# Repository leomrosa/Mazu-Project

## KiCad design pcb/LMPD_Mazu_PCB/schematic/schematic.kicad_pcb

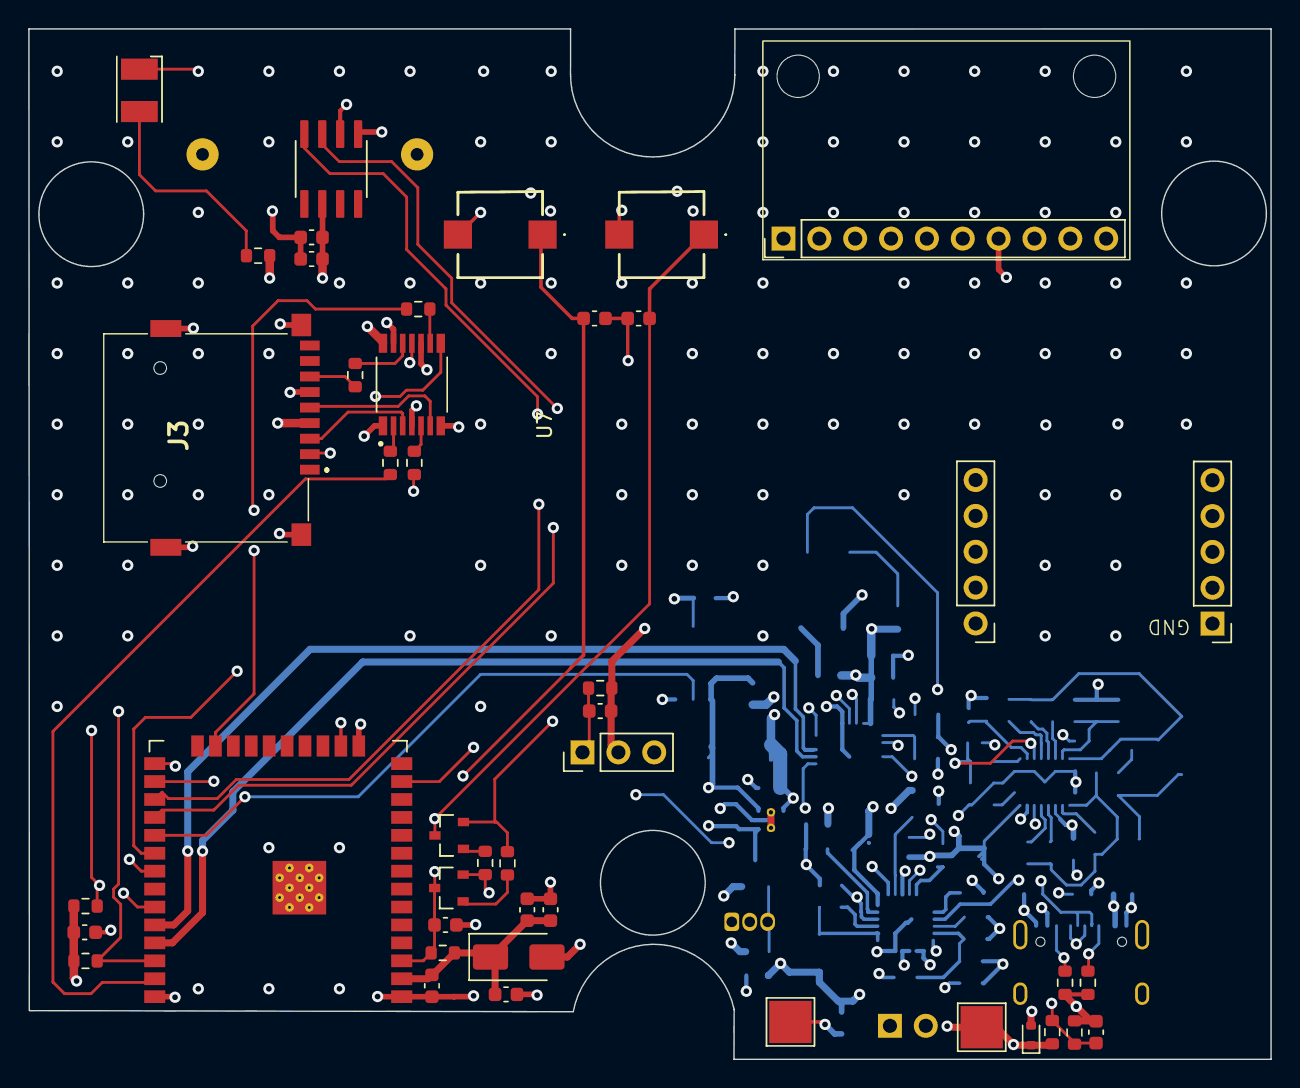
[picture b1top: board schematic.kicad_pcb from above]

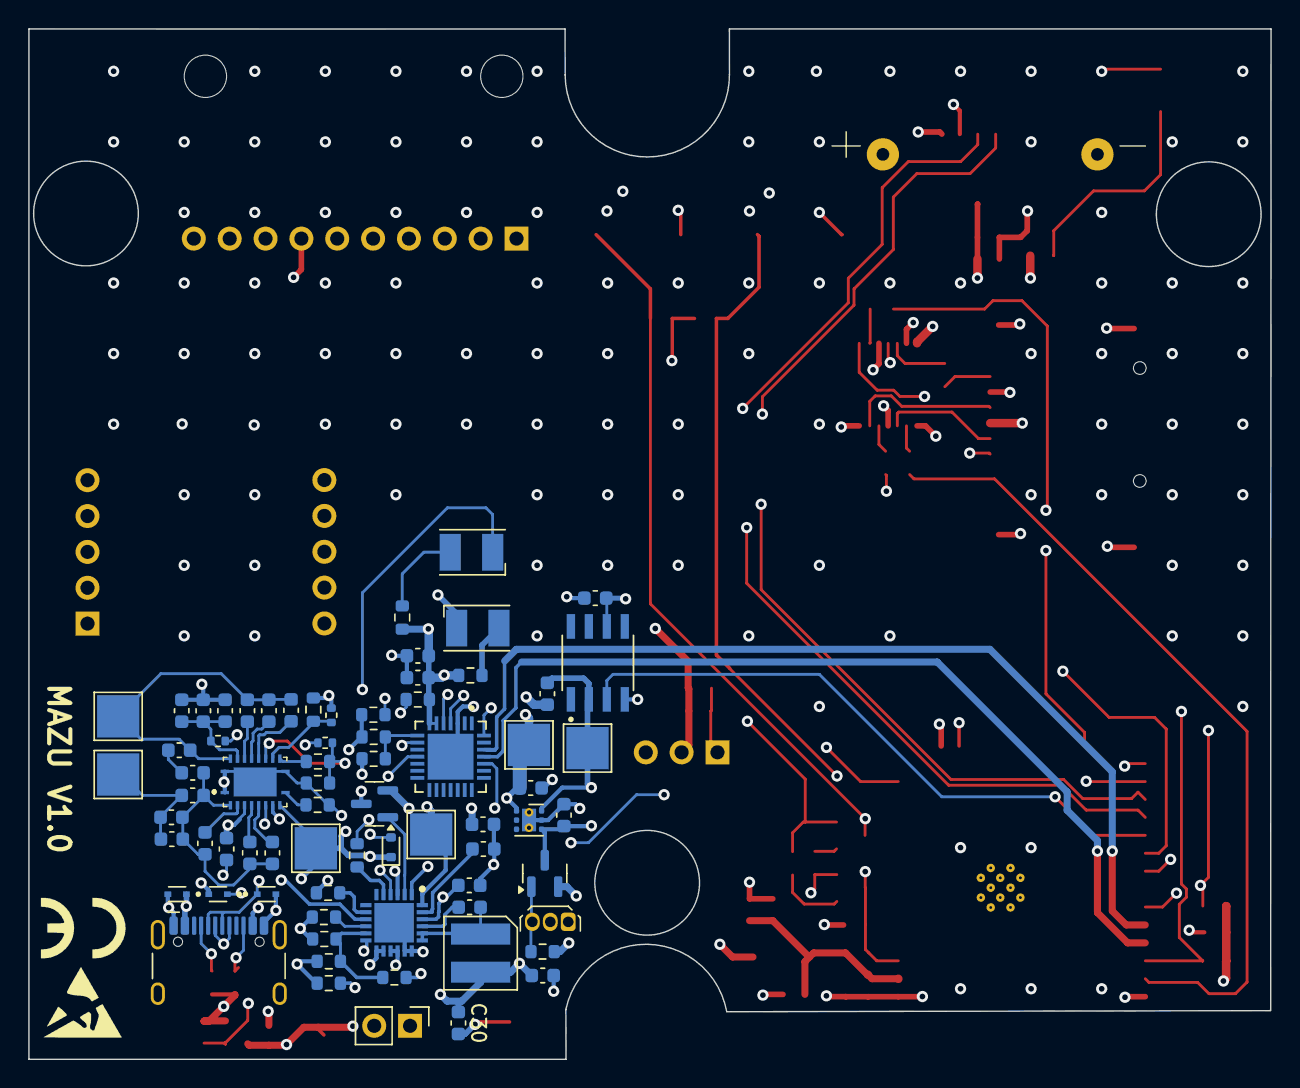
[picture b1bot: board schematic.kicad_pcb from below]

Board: 6 copper layers, 88.0 x 73.0 mm, 115 parts (72 on the bottom side), 77 nets.

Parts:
BT1: Battery_Cell; Panasonic BR1632
C1: 2.2u; C_0603_1608Metric
C2: 4.7u; C_0603_1608Metric
C3, C4, C5, C6, C7, C8, C11, C12, C16, C25, C31, C32, C33, C34, C36, C38: 100n; C_0603_1608Metric
C9, C30: 47u; C_0603_1608Metric
C10, C39: 470n; C_0603_1608Metric
C13: 1u; C_0603_1608Metric
C14, C15, C17, C19: 22n; C_0603_1608Metric
C18: 2.2n; C_0603_1608Metric
C20, C21, C22: 10n; C_0603_1608Metric
C23, C24, C26, C27, C35, C37: 10u; C_0603_1608Metric
C28: 47n; C_0603_1608Metric
C29: 4.7u - 10v; C_0603_1608Metric
D1, D5: CPDU12V0U-HF; D_SOD-523
D2, D3, D4: LESD5D5.0CT1G; TVS_LESD5D5.0CT1G
D6: VLMT3100-GS08; LED_PLCC-2_3.4x3.0mm_KA
D7, D8: VLMC3100-GS08; LED_PLCC-2_3.4x3.0mm_KA
D9: B340A-E3/61T; D_SMA
IC2: BQ25616RTWR; QFN50P400X400X80-25N-D
J1: Batt; PinHeader_1x02_P2.54mm_Vertical
J1_TMP1: Conn_01x03_Male; PinHeader_1x03_P2.54mm_Vertical
J2: GT-USB-7010ASV; USB_C_Receptacle_HCTL_HC-TYPE-C-16P-01A
J3: TF-15X15; TF15X15
L1: 1uH; inductor_bourns_4x4
Q1, Q2: SS8050-G; TRANS_SS8050-G
Q3: IRLML6344TRPBF; SOT-23
Q4: SSM3J338R,LF; SOT-23
R1, R2, R32: 5.1k; R_0603_1608Metric
R3, R4, R6, R8, R10, R11, R21, R28, R30, R34, R35, R39: 10k; R_0603_1608Metric
R5, R12, R13: 4.7k; R_0603_1608Metric
R7, R9, R31: 680; R_0603_1608Metric
R17, R18, R19, R20: 330; R_0603_1608Metric
R22, R23: 220; R_0603_1608Metric
R24: 2.4k; R_0603_1608Metric
R25, R26, R27: 12k; R_0402_1005Metric
R29: 560; R_0603_1608Metric
R33: 33k; R_0603_1608Metric
R36: 22.1k; R_0603_1608Metric
R37: 47.5k; R_0603_1608Metric
R38: 2k; R_0603_1608Metric
SW1, SW2: SW_Push; EVPASAC1A
TP1, TP2, TP3, TP4, TP5, TP6, TP7, TP8: TestPoint_Pad_3.0x3.0mm
U1: REF196GSZ-REEL; SOIC127P600X175-8N
U2: SS460S; TO-92Flat
U3: LP5912-3.3DRV; LP5912
U4: GY-9250
U5: 74LVC125APW,118; IC_74LVC125APW,118
U6: BQ51050BRHLR
U7: ESP32-WROOM-32D
U8: CP2102N-A02-GQFN28; QFN50P500X500X80-29N
U9: GPS-AIR530; GPS_Air530
U10: DS3231MZ+TRL; DS3231MZ_TRL

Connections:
/BATT: C13.1, D1.1 (A1), IC2.13 (BAT_1), IC2.14 (BAT_2), J1.2, R10.2, TP1.1, U6.4 (BAT)
/CTRL_GPIO: U1.3 (SHDN), U7.29 (IO5)
/DTR: Q2.2, R3.2, U8.28 (DTR)
/EN: C32.1, C33.1, Q1.3, R35.2, SW1.A1 (COM), U7.3 (EN)
/ESP32_WROOM_32D/IO14: C4.1, R10.1, R11.2, U7.13 (IO14)
/ESP32_WROOM_32D/VDD_3V3: C8.1, C9.1, C34.1, C35.1, D9.1 (K), R35.1, U7.2 (VDD)
/GPS_RXD: U7.28 (IO17), U9.7 (GPS_RXD)
/GPS_TXD: U7.27 (IO16), U9.6 (GPS_TXD)
/IIC_SCL: R12.2, U4.3 (SCL), U7.36 (IO22), U10.8 (SCL)
/IIC_SDA: R13.2, U4.4 (SDA), U7.33 (IO21), U10.7 (SDA)
/IO0: C36.1, Q2.3, SW2.A1 (COM), U7.25 (IO0)
/PRE_VCC: C30.1, C31.1, IC2.15 (SYS_1), IC2.16 (SYS_2), L1.2, Q4.2 (S), R8.2, U2.1 (IN)
/RTS: Q1.2, R4.2, U8.24 (RTS)
/SPI_CS: R19.1, U7.23 (IO15)
/SPI_MISO: U5.11 (4Y), U7.31 (IO19)
/SPI_MOSI: R17.1, U7.37 (IO23)
/SPI_SCK: R18.1, U7.30 (IO18)
/STAT: D7.1 (K), R28.1, U7.16 (IO13)
/TMP_DATA: C3.1, J1_TMP1.1, R5.1, U7.26 (IO4)
/UART_PROG_RX: U7.35 (TXD0/IO1), U8.25 (RXD)
/UART_PROG_TX: U7.34 (RXD0/IO3), U8.26 (TXD)
/USB5V: D4.1, D5.1 (A1), IC2.1 (VAC), J2.A4 (VBUS), J2.A9 (VBUS), J2.B4 (VBUS), J2.B9 (VBUS), Q3.3 (D), R36.1, TP3.1, U6.9 (AD)
/USBD+: D2.1, IC2.3 (D+), J2.A6 (D+), J2.B6 (D+), U8.4 (D+)
/USBD-: D3.1, IC2.4 (D-), J2.A7 (D-), J2.B7 (D-), U8.5 (D-)
/VCC_RAW: C1.1, C5.1, Q4.3 (D), TP7.1, U1.2 (VIN), U3.4 (EN), U3.6 (IN)
/VREF_3V3: C6.1, C7.1, C11.1, C12.1, C37.1, C38.1, D9.2 (A), J3.4 (VDD), R7.2, R9.2, R12.1, R13.1, R21.1, R38.1, TP8.1, U3.1 (OUT), U4.1 (VCC), U4.7 (ADO), U5.14 (VCC), U8.6 (VDD), U8.7 (VREGIN), U9.3 (3V3), U9.5 (VBACKUP), U10.2 (VCC)
/VREF_TMP_3V3: C2.1, C3.2, J1_TMP1.2, R5.2, U1.6 (VOUT)
/WRL_EN: IC2.9 (~CE), U6.8 (~AD-EN)
/batery_module/ACDRV: IC2.2 (ACDRV), Q3.1 (G)
/batery_module/VIN: C26.1, IC2.24 (VBUS), Q3.2 (S), TP4.1
/rtc_ds3231/BAT_CELL+: BT1.1 (+), U10.6 (VBAT)
/sd_card/CS_LLS: J3.2 (CD/DAT3), U5.8 (3Y)
/sd_card/DI_LLS: J3.3 (CMD), U5.3 (1Y)
/sd_card/DO_LLS: J3.7 (DAT0), R20.1
/sd_card/SCK_LLS: J3.5 (CLX), U5.6 (2Y)
/wireless_charging/AC1: C10.2, C14.1, C15.1, C16.2, C17.2, C18.2, C21.2, U6.2 (AC1)
/wireless_charging/CLAMP1: C10.1, U6.5 (CLAMP1)
/wireless_charging/CLAMP2: C39.1, U6.16 (CLAMP2)
/wireless_charging/COIL+: C14.2, C15.2, C16.1, TP6.1
/wireless_charging/COIL-: C19.2, C20.1, C22.2, C39.2, TP5.1, U6.19 (AC2)
/wireless_charging/NTC: R6.1, R25.1, U6.13 (TS/CTRL)
/wireless_charging/RECT: C23.1, C24.1, C25.1, R26.1, U6.18 (RECT)
/wireless_charging/TERM: R24.2, U6.10 (TERM)
/wireless_charging/~CHG_PIN: D6.1 (K), U6.7 (~CHG)
GNDREF: BT1.2 (-), C1.2, C2.2, C4.2, C5.2, C6.2, C7.2, C8.2, C9.2, C11.2, C12.2, C13.2, C23.2, C24.2, C25.2, C26.2, C27.2, C29.2, C30.2, C31.2, C32.2, C33.2, C34.2, C35.2, C36.2, C37.2, C38.2, D1.2 (A2), D2.2, D3.2, D4.2, D5.2 (A2), D8.1 (K), IC2.17 (GND_1), IC2.18 (GND_2), IC2.25 (EP), J1.1, J1_TMP1.3, J2.A1 (GND), J2.A12 (GND), J2.B1 (GND), J2.B12 (GND), J2.S1 (SHIELD), J3.6 (VSS), J3.MP1, J3.MP2, J3.MP3, J3.MP4, R1.1, R2.1, R6.2, R11.1, R23.1, R24.1, R25.2, R29.2, R30.2, R31.2, R33.1, R34.1, R37.2, R39.2, SW1.B1 (NO), SW2.B1 (NO), TP2.1, U1.4 (GND), U2.2, U3.5 (GND), U3.7 (EP), U4.2 (GND), U5.1 (1~OE), U5.4 (2~OE), U5.7 (GND), U5.10 (3~OE), U5.13 (4~OE), U6.1 (PGND), U6.11 (EN2), U6.20 (PGND), U6.21 (PGND), U7.1 (GND), U7.15 (GND), U7.38 (GND), U7.39 (GND), U8.3 (GND), U8.29 (GND), U9.1 (GND), U10.5 (GND)
unnamed: C18.1, C20.2
unnamed: D6.2 (A), R7.1
unnamed: D7.2 (A), R9.1
unnamed: D8.2 (A), R21.2
unnamed: C28.1, IC2.21 (BTST)
unnamed: IC2.10 (ICHG), R31.1
unnamed: IC2.8 (ILIM), R29.1
unnamed: C27.1, IC2.23 (PMID)
unnamed: C29.1, IC2.22 (REGN), R32.1
unnamed: IC2.5 (STAT), R28.2
unnamed: C28.2, IC2.19 (SW_1), IC2.20 (SW_2), L1.1
unnamed: IC2.11 (TS), R32.2, R33.2, R34.2
unnamed: IC2.12 (VSET), R30.1
unnamed: J2.A5 (CC1), R1.2
unnamed: J2.B5 (CC2), R2.2
unnamed: Q1.1, R3.1
unnamed: Q2.1, R4.1
unnamed: Q4.1 (G), R8.1, U2.3 (OUT)
unnamed: R26.2, R27.1
unnamed: R17.2, U5.2 (1A)
unnamed: R18.2, U5.5 (2A)
unnamed: R19.2, U5.9 (3A)
unnamed: R20.2, U5.12 (4A)
unnamed: C21.1, U6.3 (BOOT1)
unnamed: C22.1, U6.17 (BOOT2)
unnamed: C17.1, U6.6 (COMM1)
unnamed: C19.1, U6.15 (COMM2)
unnamed: R22.2, R23.2, R27.2, U6.14 (FOD)
unnamed: R22.1, U6.12 (ILIM)
unnamed: R36.2, R37.1, U8.8 (VBUS)
unnamed: R38.2, U8.9 (~RST)
unnamed: R39.1, U8.11 (~SUSPEND)

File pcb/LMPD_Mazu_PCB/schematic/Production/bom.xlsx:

Comment | Designator | Footprint | JLCPCB Part
Battery_Cell | BT1 | Panasonic BR1632
2.2u | C1 | C_0603_1608Metric | CS1608X5R225K100NRB
4.7u | C2 | C_0603_1608Metric | TCC0603X5R475K250CT
100n | C3 | C_0603_1608Metric | CC0603KRX7R9BB104
100n | C4 | C_0603_1608Metric | CC0603KRX7R9BB104
100n | C5 | C_0603_1608Metric | CC0603KRX7R9BB104
100n | C6 | C_0603_1608Metric | CC0603KRX7R9BB104
100n | C7 | C_0603_1608Metric | CC0603KRX7R9BB104
100n | C8 | C_0603_1608Metric | CC0603KRX7R9BB104
47u | C9 | C_0603_1608Metric | GRM188R60J476ME15D
470n | C10 | C_0603_1608Metric | CL10B474KA8NNNC
100n | C11 | C_0603_1608Metric | CC0603KRX7R9BB104
100n | C12 | C_0603_1608Metric | CC0603KRX7R9BB104
1u | C13 | C_0603_1608Metric | 0603B105K250NT
22n | C14 | C_0603_1608Metric | 0603B223K500NT
22n | C15 | C_0603_1608Metric | 0603B223K500NT
100n | C16 | C_0603_1608Metric | CC0603KRX7R9BB104
22n | C17 | C_0603_1608Metric | 0603B223K500NT
2.2n | C18 | C_0603_1608Metric | CC0603JRNPO9BN222
22n | C19 | C_0603_1608Metric | 0603B223K500NT
10n | C20 | C_0603_1608Metric | 0603B103K500NT
10n | C21 | C_0603_1608Metric | 0603B103K500NT
10n | C22 | C_0603_1608Metric | 0603B103K500NT
10u | C23 | C_0603_1608Metric | 0603X106M250NT
10u | C24 | C_0603_1608Metric | 0603X106M250NT
100n | C25 | C_0603_1608Metric | CC0603KRX7R9BB104
10u | C26 | C_0603_1608Metric | 0603X106M250NT
10u | C27 | C_0603_1608Metric | 0603X106M250NT
47n | C28 | C_0603_1608Metric | 0603B473K500NT
4.7u - 10v | C29 | C_0603_1608Metric | GRM188R61A475KE15D
47u | C30 | C_0603_1608Metric | GRM188R60J476ME15D
100n | C31 | C_0603_1608Metric | CC0603KRX7R9BB104
100n | C32 | C_0603_1608Metric | CC0603KRX7R9BB104
100n | C33 | C_0603_1608Metric | CC0603KRX7R9BB104
100n | C34 | C_0603_1608Metric | CC0603KRX7R9BB104
10u | C35 | C_0603_1608Metric | 0603X106M250NT
100n | C36 | C_0603_1608Metric | CC0603KRX7R9BB104
10u | C37 | C_0603_1608Metric | 0603X106M250NT
100n | C38 | C_0603_1608Metric | CC0603KRX7R9BB104
470n | C39 | C_0603_1608Metric | CL10B474KA8NNNC
CPDU12V0U-HF | D1 | D_SOD-523 | CPDU12V0U-HF
LESD5D5.0CT1G | D2 | TVS_LESD5D5.0CT1G | LESD5D5.0CT1G
LESD5D5.0CT1G | D3 | TVS_LESD5D5.0CT1G | LESD5D5.0CT1G
LESD5D5.0CT1G | D4 | TVS_LESD5D5.0CT1G | LESD5D5.0CT1G
CPDU12V0U-HF | D5 | D_SOD-523 | CPDU12V0U-HF
VLMT3100-GS08 | D6 | LED_PLCC-2_3.4x3.0mm_KA | VLMT3100-GS08
VLMC3100-GS08 | D7 | LED_PLCC-2_3.4x3.0mm_KA | VLMC3100-GS08
VLMC3100-GS08 | D8 | LED_PLCC-2_3.4x3.0mm_KA | VLMC3100-GS08
B340A-E3/61T | D9 | D_SMA | B340A-E3/61T
BQ25616RTWR | IC2 | QFN50P400X400X80-25N-D | BQ25616RTWR
Batt | J1 | PinHeader_1x02_P2.54mm_Vertical
Conn_01x03_Male | J1_TMP1 | PinHeader_1x03_P2.54mm_Vertical
GT-USB-7010ASV | J2 | USB_C_Receptacle_HCTL_HC-TYPE-C-16P-01A | GT-USB-7010ASV
TF-15X15 | J3 | TF15X15 | TF-15x15
1uH | L1 | inductor_bourns_4x4 | WPN4020H1R0MT
SS8050-G | Q1 | TRANS_SS8050-G | SS8050-G
SS8050-G | Q2 | TRANS_SS8050-G | SS8050-G
IRLML6344TRPBF | Q3 | SOT-23 | IRLML6344TRPBF
SSM3J338R,LF | Q4 | SOT-23 | SSM3J338R,LF
5.1k | R1 | R_0603_1608Metric | 0603WAF5101T5E
5.1k | R2 | R_0603_1608Metric | 0603WAF5101T5E
10k | R3 | R_0603_1608Metric | FRC0603J103TS
10k | R4 | R_0603_1608Metric | FRC0603J103TS
4.7k | R5 | R_0603_1608Metric | AC0603FR-074K7L
10k | R6 | R_0603_1608Metric | FRC0603J103TS
680 | R7 | R_0603_1608Metric | 0603WAF6800T5E
10k | R8 | R_0603_1608Metric | FRC0603J103TS
680 | R9 | R_0603_1608Metric | 0603WAF6800T5E
10k | R10 | R_0603_1608Metric | FRC0603J103TS
10k | R11 | R_0603_1608Metric | FRC0603J103TS
4.7k | R12 | R_0603_1608Metric | AC0603FR-074K7L
4.7k | R13 | R_0603_1608Metric | AC0603FR-074K7L
330 | R17 | R_0603_1608Metric | 0603WAF3300T5E
330 | R18 | R_0603_1608Metric | 0603WAF3300T5E
330 | R19 | R_0603_1608Metric | 0603WAF3300T5E
330 | R20 | R_0603_1608Metric | 0603WAF3300T5E
10k | R21 | R_0603_1608Metric | FRC0603J103TS
220 | R22 | R_0603_1608Metric | FRC0603J221 TS
220 | R23 | R_0603_1608Metric | FRC0603J221 TS
2.4k | R24 | R_0603_1608Metric | RTT03242JTP
12k | R25 | R_0402_1005Metric | 0402WGF1202TCE
12k | R26 | R_0402_1005Metric | 0402WGF1202TCE
12k | R27 | R_0402_1005Metric | 0402WGF1202TCE
10k | R28 | R_0603_1608Metric | FRC0603J103TS
560 | R29 | R_0603_1608Metric | 0603WAF5600T5E
10k | R30 | R_0603_1608Metric | FRC0603J103TS
680 | R31 | R_0603_1608Metric | 0603WAF6800T5E
5.1k | R32 | R_0603_1608Metric | 0603WAF5101T5E
33k | R33 | R_0603_1608Metric | WR06X3302FTL
10k | R34 | R_0603_1608Metric | FRC0603J103TS
10k | R35 | R_0603_1608Metric | FRC0603J103TS
22.1k | R36 | R_0603_1608Metric | 0603WAF2212T5E
47.5k | R37 | R_0603_1608Metric | FRC0603F4752TS
2k | R38 | R_0603_1608Metric | RS-03K2001FT
10k | R39 | R_0603_1608Metric | FRC0603J103TS
SW_Push | SW1 | EVPASAC1A | EVP-ASAC1A
SW_Push | SW2 | EVPASAC1A | EVP-ASAC1A
~ | TP1 | TestPoint_Pad_3.0x3.0mm
~ | TP2 | TestPoint_Pad_3.0x3.0mm
~ | TP3 | TestPoint_Pad_3.0x3.0mm
~ | TP4 | TestPoint_Pad_3.0x3.0mm
~ | TP5 | TestPoint_Pad_3.0x3.0mm
~ | TP6 | TestPoint_Pad_3.0x3.0mm
~ | TP7 | TestPoint_Pad_3.0x3.0mm
~ | TP8 | TestPoint_Pad_3.0x3.0mm
REF196GSZ-REEL | U1 | SOIC127P600X175-8N | REF196GSZ-REEL
SS460S | U2 | TO-92Flat | SS460S
LP5912-3.3DRV | U3 | LP5912 | LP5912-3.3DRVR
GY-9250 | U4 | GY-9250
74LVC125APW,118 | U5 | IC_74LVC125APW,118 | 74LVC125APW,118
BQ51050BRHLR | U6 | BQ51050BRHLR | BQ51050BRHLR
ESP32-WROOM-32D | U7 | ESP32-WROOM-32D | ESP32-WROOM-32D-N4
CP2102N-A02-GQFN28 | U8 | QFN50P500X500X80-29N | CP2102N-A02-GQFN28R
GPS-AIR530 | U9 | GPS_Air530
DS3231MZ+TRL | U10 | DS3231MZ_TRL | DS3231MZ+TRL

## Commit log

2024-10-28 Adicionei codigo ESP
2024-10-28 Adicinei os Results
2024-10-28 Adicioneo«i codigo da app android e ficheiros kicad
2024-10-28 Removi
2024-10-28 Adicionei ficheiros kicad
